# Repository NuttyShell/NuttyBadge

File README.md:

# NuttyBadge
NuttyBadge: A NuttyShell crafted security and hardware multi-tool. Open-sourced Hardware and Software.

## Hardware
[Click here for Hardware](NuttyHardware): Full Schematic and PCBs, along with BOM list

## Software
[Click here for Software](NuttyOS): Full Software based on ESP-IDF and FreeRTOS

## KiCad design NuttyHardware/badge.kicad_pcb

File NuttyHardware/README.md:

# NuttyBadge/NuttyHardware

---
# Hardware Changelog

## Latest hardware revision: Rev. C (May-2026)

Compared to Rev. B (June-2025), NuttyBadge Revision C has the following changes:

- Switched the main screen from LCD to OLED. SPI is still used, code changes are implemented to support both version of the NuttyBadge via a preprocessor marco.

- The physical screen size of the OLED screen is smaller, but the resolution is kept the same (128x64). Compared to the original LCD screen, OLED screen provides way better contrast level, no ghosting, and supports way higher framerate, which could potentially enable better experiences for fast moving objects like gaming scenes.

- As OLED is self-illuminating, there is no backlight. So now R11, R18 and Q2 are unpopulated. LCD_BL_PWM is unused and can be hacked for other purposes.

- Fixed a minor issue in Rev. B where the bypass capacitor (C49 and C51) for Y1 (USB Hub CH334R [U10]'s 12MHz USB Crystal) is wrong. With a 12pF shunt capacitance of the crystal, there is no need to populate C49 and C51. Just relying on the internal capacitors in the CH334R is sufficient.

---

Compared to Rev. A (Initial Version of June-2024), NuttyBadge Revision B has the following changes:

- LuatOS ESP32 Module has stopped production entirely. As the manufacturer refuses to sell the module with even no MOQ figures, we are forced to switch to use another module. We have completely abandoned the usage of 3rd party module and stick with original `ESP32-S3-WROOM-1-N16R8` module to avoid future supply chain problem.

- We included a USB HUB chip (CH334R) [U10] to allow the simultaneously usage of both usb-to-serial chip (CH343P) [U11] and ESP32S3 onboard USB device.

- Auto reset and program mode via DTR/RTS pins are fully implemented.

- Note: C49 and C51 values are incorrect, as CH334R contains an internal bypass cap for the crystal. The distributed boards had C49 and C51 removed. This will be fixed in NuttyBadge Rev. C.

- In terms of schematic hierarchy, we now have a dedicated schematic sheet for the ESP32S3 part of the circuit due to above reasons.

- Audio circuit is optmized and simplified. Now we just use a single N-FET (AO3400A) [Q4] to drive the buzzer [BZ1]. We expect this will further improve the sound quality and efficiency of the circuit.

- A Camera port is included in Rev. B. Although one already provided in the LuatOS module, the pins used might clash with PSRAM and are not carefully considered. Tested with OV2640 with fair results.

- Two LDOs are included to generate 1.2V and 2.8V rails to enable the usage of camera.

- LCD Backlight are driven with N-FET, this will make the driving circuit more efficient.

- For the main battery buck-boost converter, we have switched L1 from 2.2uH to 3.3uH, to provide better voltage ripple figures and reduce conduction losses in the expense of load transient response.

- We also wired the PS pin of TPS63001 to the positive rail, enabling power save mode to allow the overall circuit saving more power.

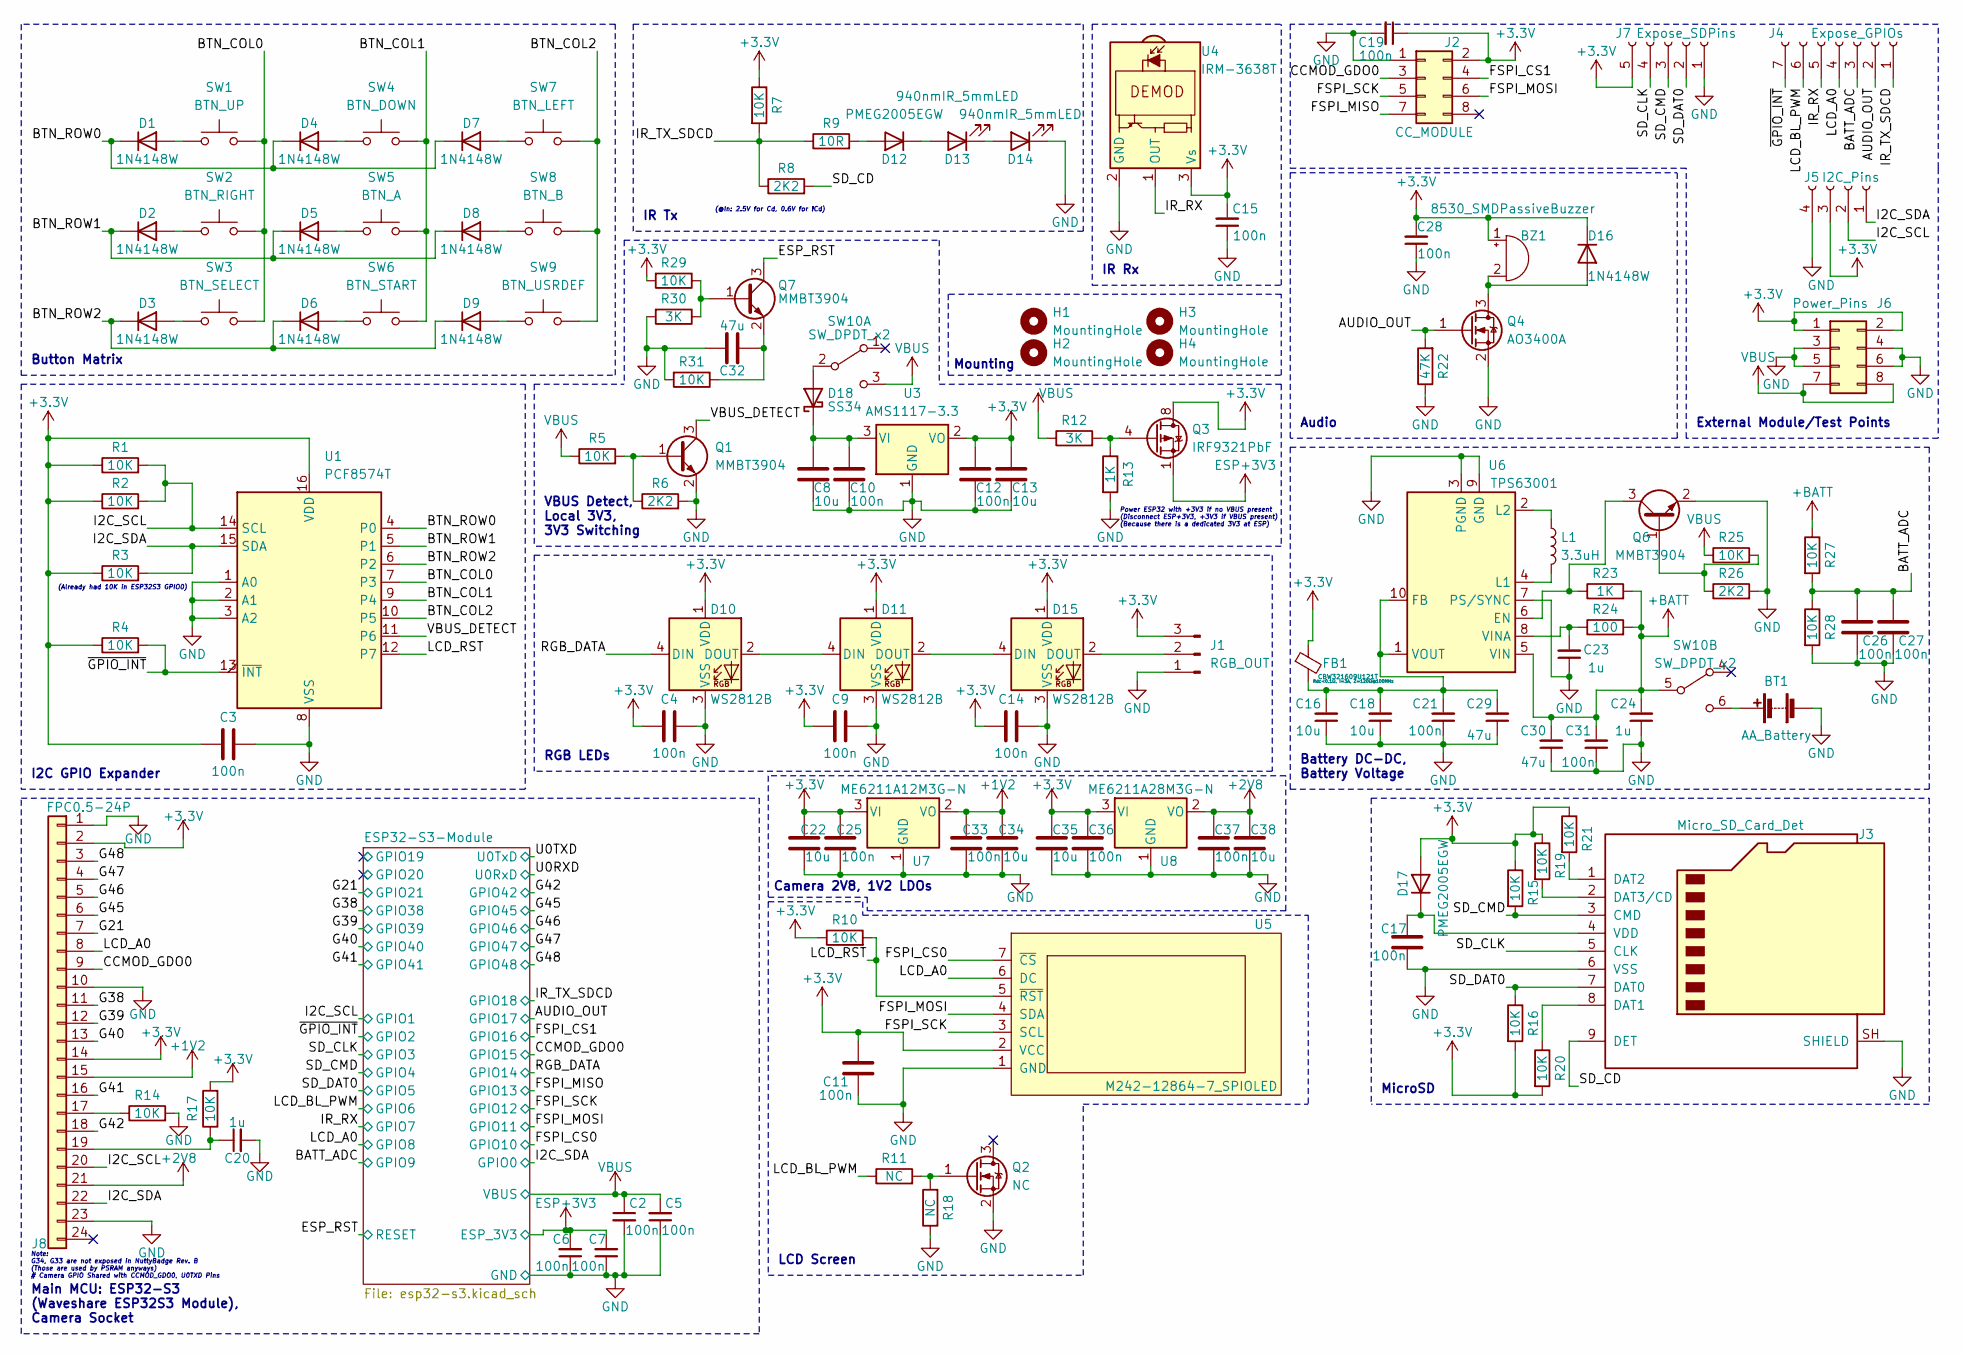
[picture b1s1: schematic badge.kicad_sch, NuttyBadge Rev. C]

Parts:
BT1: AA_Battery; BatteryHolder_2AA
BZ1: 8530_SMDPassiveBuzzer; MagneticBuzzer_Kobitone_254-EMB84Q-RO
C2, C3, C4, C5, C6, C7, C9, C10, C11, C12, C14, C15, C17, C19, C21, C25, C26, C27, C28, C31, C33, C36, C37: 100n; C_1206_3216Metric_Pad1.33x1.80mm_HandSolder
C8, C13, C16, C18, C22, C34, C35, C38: 10u; C_1206_3216Metric_Pad1.33x1.80mm_HandSolder
C20, C23, C24: 1u; C_1206_3216Metric_Pad1.33x1.80mm_HandSolder
C29, C30, C32: 47u; C_1206_3216Metric_Pad1.33x1.80mm_HandSolder
D1, D2, D3, D4, D5, D6, D7, D8, D9, D16: 1N4148W; D_SOD-123-BigDiodeSilkscreen
D10, D11, D15: WS2812B; LED_WS2812B_PLCC4_5.0x5.0mm_P3.2mm-TriangleSilkscreen
D12, D17: PMEG2005EGW; D_SOD-123-BigDiodeSilkscreen
D13, D14: 940nmIR_5mmLED; LED_D5.0mm_Horizontal_O3.81mm_Z3.0mm
D18: SS34; D_SMA_Handsoldering-BigDiodeSilkscreen
FB1: CBW321609U121T; L_1206_3216Metric_Pad1.42x1.75mm_HandSolder
H1, H2, H3, H4: MountingHole; MountingHole_3.2mm_M3_ISO7380
J1: RGB_OUT; PinHeader_1x03_P2.54mm_Vertical
J2: CC_MODULE; PinSocket_2x04_P2.54mm_Vertical_PinNumberFlipped
J3: Micro_SD_Card_Det; Conn_uSDcard
J4: Expose_GPIOs; PinHeader_1x07_P2.54mm_Vertical
J5: I2C_Pins; PinSocket_1x04_P2.54mm_Vertical
J6: Power_Pins; PinSocket_2x04_P2.54mm_Vertical_PinNumberFlipped
J7: Expose_SDPins; PinHeader_1x05_P2.54mm_Vertical
J8: FPC0.5-24P; Jushuo_AFC07-S24FCA-00_1x24-1MP_P0.50_Horizontal
L1: 3.3uH; L_Wuerth_HCI-1040
Q1, Q6, Q7: MMBT3904; SOT-23
Q2: NC; SOT-23
Q3: IRF9321PbF; SOIC-8_3.9x4.9mm_P1.27mm
Q4: AO3400A; SOT-23
R1, R2, R3, R4, R5, R7, R10, R14, R15, R16, R17, R19, R20, R21, R25, R27, R28, R29, R31: 10K; R_1206_3216Metric_Pad1.30x1.75mm_HandSolder
R6, R8, R26: 2K2; R_1206_3216Metric_Pad1.30x1.75mm_HandSolder
R9: 10R; R_1206_3216Metric_Pad1.30x1.75mm_HandSolder
R11, R18: NC; R_1206_3216Metric_Pad1.30x1.75mm_HandSolder
R12, R30: 3K; R_1206_3216Metric_Pad1.30x1.75mm_HandSolder
R13, R23: 1K; R_1206_3216Metric_Pad1.30x1.75mm_HandSolder
R22: 47K; R_1206_3216Metric_Pad1.30x1.75mm_HandSolder
R24: 100; R_1206_3216Metric_Pad1.30x1.75mm_HandSolder
SW1: BTN_UP; SW_Push_1P1T_NO_CK_PTS125Sx43PSMTR_NoHoles
SW2: BTN_RIGHT; SW_Push_1P1T_NO_CK_PTS125Sx43PSMTR_NoHoles
SW3: BTN_SELECT; SW_Push_1P1T_NO_CK_PTS125Sx43PSMTR_NoHoles
SW4: BTN_DOWN; SW_Push_1P1T_NO_CK_PTS125Sx43PSMTR_NoHoles
SW5: BTN_A; SW_Push_1P1T_NO_CK_PTS125Sx43PSMTR_NoHoles
SW6: BTN_START; SW_Push_1P1T_NO_CK_PTS125Sx43PSMTR_NoHoles
SW7: BTN_LEFT; SW_Push_1P1T_NO_CK_PTS125Sx43PSMTR_NoHoles
SW8: BTN_B; SW_Push_1P1T_NO_CK_PTS125Sx43PSMTR_NoHoles
SW9: BTN_USRDEF; SW_Push_1P1T_NO_CK_PTS125Sx43PSMTR_NoHoles
SW10: SW_DPDT_x2; SW_DPDT_Power_Switch
U1: PCF8574T; SOIC-16W_7.5x10.3mm_P1.27mm
U3: AMS1117-3.3; SOT-223-3_TabPin2
U4: IRM-3638T; Vishay_MINICAST-3Pin
U5: M242-12864-7_SPIOLED; M242-12864-7
U6: TPS63001; Texas_DRC0010J_ThermalVias_LargeHoles
U7: ME6211A12M3G-N; SOT-23-3
U8: ME6211A28M3G-N; SOT-23-3

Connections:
+1V2: C33.2, C34.2, J8.15, U7.2 (VO)
+2V8: C37.2, C38.2, J8.21, U8.2 (VO)
+3.3V: BZ1.1 (-), C3.1, C4.1, C9.1, C11.2, C12.2, C13.2, C14.1, C15.2, C19.1, C22.2, C25.2, C28.2, C35.2, C36.2, D10.1 (VDD), D11.1 (VDD), D15.1 (VDD), D16.1 (K), D17.2 (A), FB1.1, J1.3, J2.2, J5.3, J6.1, J6.2, J7.5, J8.2, J8.14, Q3.5 (D), Q3.6 (D), Q3.7 (D), Q3.8 (D), R1.1, R2.1, R3.1, R4.1, R7.1, R10.1, R15.1, R16.2, R17.2, R19.1, R20.2, R21.1, R29.2, U1.16 (VDD), U3.2 (VO), U4.3 (Vs), U5.2 (VCC), U7.3 (VI), U8.3 (VI)
+BATT: C24.2, C30.2, C31.2, R23.2, R24.2, R27.1, SW10.5 (B), U6.5 (VIN)
/AUDIO_OUT: J4.2, Q4.1 (G), R22.2; also elsewhere on the board
/BATT_ADC: C26.2, C27.2, J4.3, R27.2, R28.1; also elsewhere on the board
/BTN_COL0: SW1.2, SW2.2, SW3.2, U1.7 (P3)
/BTN_COL1: SW4.2, SW5.2, SW6.2, U1.9 (P4)
/BTN_COL2: SW7.2, SW8.2, SW9.2, U1.10 (P5)
/BTN_ROW0: D1.1 (K), D4.1 (K), D7.1 (K), U1.4 (P0)
/BTN_ROW1: D2.1 (K), D5.1 (K), D8.1 (K), U1.5 (P1)
/BTN_ROW2: D3.1 (K), D6.1 (K), D9.1 (K), U1.6 (P2)
/CCMOD_GDO0: J2.3, J8.9; also elsewhere on the board
/ESP_RST: Q7.3 (C); also elsewhere on the board
/FSPI_CS0: U5.7 (~CS); also elsewhere on the board
/FSPI_CS1: J2.4; also elsewhere on the board
/FSPI_MISO: J2.7; also elsewhere on the board
/FSPI_MOSI: J2.6, U5.4 (SDA); also elsewhere on the board
/FSPI_SCK: J2.5, U5.3 (SCL); also elsewhere on the board
/G21: J8.7; also elsewhere on the board
/G38: J8.11; also elsewhere on the board
/G39: J8.12; also elsewhere on the board
/G40: J8.13; also elsewhere on the board
/G41: J8.16; also elsewhere on the board
/G42: J8.18; also elsewhere on the board
/G45: J8.6; also elsewhere on the board
/G46: J8.5; also elsewhere on the board
/G47: J8.4; also elsewhere on the board
/G48: J8.3; also elsewhere on the board
/I2C_SCL: J5.2, J8.20, R1.2, R2.2, U1.14 (SCL); also elsewhere on the board
/I2C_SDA: J5.1, J8.22, R3.2, U1.15 (SDA); also elsewhere on the board
/IR_RX: J4.5, U4.1 (OUT); also elsewhere on the board
/IR_TX_SDCD: J4.1, R7.2, R8.1, R9.1; also elsewhere on the board
/LCD_A0: J4.4, J8.8, U5.6 (DC); also elsewhere on the board
/LCD_BL_PWM: J4.6, R11.1; also elsewhere on the board
/LCD_RST: R10.2, U1.12 (P7), U5.5 (~RST)
/RGB_DATA: D10.4 (DIN); also elsewhere on the board
/SD_CD: J3.9 (DET), R8.2
/SD_CLK: J3.5 (CLK), J7.4; also elsewhere on the board
/SD_CMD: J3.3 (CMD), J7.3, R15.2; also elsewhere on the board
/SD_DAT0: J3.7 (DAT0), J7.2, R16.1; also elsewhere on the board
/VBUS_DETECT: Q1.3 (C), U1.11 (P6)
/~GPIO_INT: J4.7, R4.2, U1.13 (~INT); also elsewhere on the board
ESP+3V3: C6.2, C7.2, Q3.1 (S), Q3.2 (S), Q3.3 (S); also elsewhere on the board
GND: BT1.2 (-), C2.2, C3.2, C4.2, C5.1, C6.1, C7.1, C8.1, C9.2, C10.1, C11.1, C12.1, C13.1, C14.2, C15.1, C16.1, C17.1, C18.1, C19.2, C20.2, C21.1, C22.1, C23.1, C24.1, C25.1, C26.1, C27.1, C28.1, C29.1, C30.1, C31.1, C32.1, C33.1, C34.1, C35.1, C36.1, C37.1, C38.1, D10.3 (VSS), D11.3 (VSS), D14.1 (K), D15.3 (VSS), J1.1, J2.1, J3.6 (VSS), J3.SH (SHIELD), J5.4, J6.3, J6.4, J6.5, J6.6, J7.1, J8.1, J8.10, J8.23, Q1.2 (E), Q2.2 (S), Q4.2 (S), Q6.2 (E), R6.2, R13.2, R14.2, R18.1, R22.1, R26.2, R28.2, R30.2, R31.2, U1.1 (A0), U1.2 (A1), U1.3 (A2), U1.8 (VSS), U3.1 (GND), U4.2 (GND), U5.1 (GND), U6.3 (PGND), U6.7 (PS/SYNC), U6.9 (GND), U6.11 (PGND), U7.1 (GND), U8.1 (GND); also elsewhere on the board
unnamed: BT1.1 (+), SW10.6 (C)
unnamed: BZ1.2 (+), D16.2 (A), Q4.3 (D)
unnamed: D1.2 (A), SW1.1
unnamed: D2.2 (A), SW2.1
unnamed: D3.2 (A), SW3.1
unnamed: D4.2 (A), SW4.1
unnamed: D5.2 (A), SW5.1
unnamed: D6.2 (A), SW6.1
unnamed: D7.2 (A), SW7.1
unnamed: D8.2 (A), SW8.1
unnamed: D9.2 (A), SW9.1
unnamed: D10.2 (DOUT), D11.4 (DIN)
unnamed: D11.2 (DOUT), D15.4 (DIN)
unnamed: D12.2 (A), R9.2
unnamed: D12.1 (K), D13.2 (A)
unnamed: D13.1 (K), D14.2 (A)
unnamed: D15.2 (DOUT), J1.2
unnamed: C17.2, D17.1 (K), J3.4 (VDD)
unnamed: D18.2 (A), SW10.2 (B)
unnamed: C8.2, C10.2, D18.1 (K), U3.3 (VI)
unnamed: J3.8 (DAT1), R20.1
unnamed: J3.1 (DAT2), R21.2
unnamed: J3.2 (DAT3/CD), R19.2
unnamed: J8.17, R14.1
unnamed: C20.1, J8.19, R17.1
unnamed: Q1.1 (B), R5.2, R6.1
unnamed: Q2.1 (G), R11.2, R18.2
unnamed: Q3.4 (G), R12.2, R13.1
unnamed: Q6.1 (B), R25.2, R26.1
unnamed: Q6.3 (C), R23.1, U6.6 (EN)
unnamed: Q7.1 (B), R29.1, R30.1
unnamed: C32.2, Q7.2 (E), R31.1
unnamed: C16.2, C18.2, C21.2, C29.2, FB1.2, U6.1 (VOUT), U6.10 (FB)
unnamed: L1.2, U6.4 (L1)
unnamed: L1.1, U6.2 (L2)
unnamed: C23.2, R24.1, U6.8 (VINA)
VBUS: C2.1, C5.2, J6.7, J6.8, R5.1, R12.1, R25.1, SW10.3 (C); also elsewhere on the board

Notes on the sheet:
Button Matrix
IR Rx
(@In: 2.5V for Cd, 0.6V for !Cd)
(Already had 10K in ESP32S3 GPIO0)
External Module/Test Points
Battery DC-DC, Battery Voltage
Main MCU: ESP32-S3 (Waveshare ESP32S3 Module), Camera Socket
Mounting
Audio
Note: G34, G33 are not exposed in NuttyBadge Rev. B (Those are used by PSRAM anyways) # Camera GPIO Shared with CCMOD_GDO0, U0TXD Pins
VBUS Detect, Local 3V3, 3V3 Switching
IR Tx
MicroSD
LCD Screen
Power ESP32 with +3V3 if no VBUS present (Disconnect ESP+3V3, +3V3 if VBUS present) (Because there is a dedicated 3V3 at ESP)
I2C GPIO Expander
Camera 2V8, 1V2 LDOs
RGB LEDs

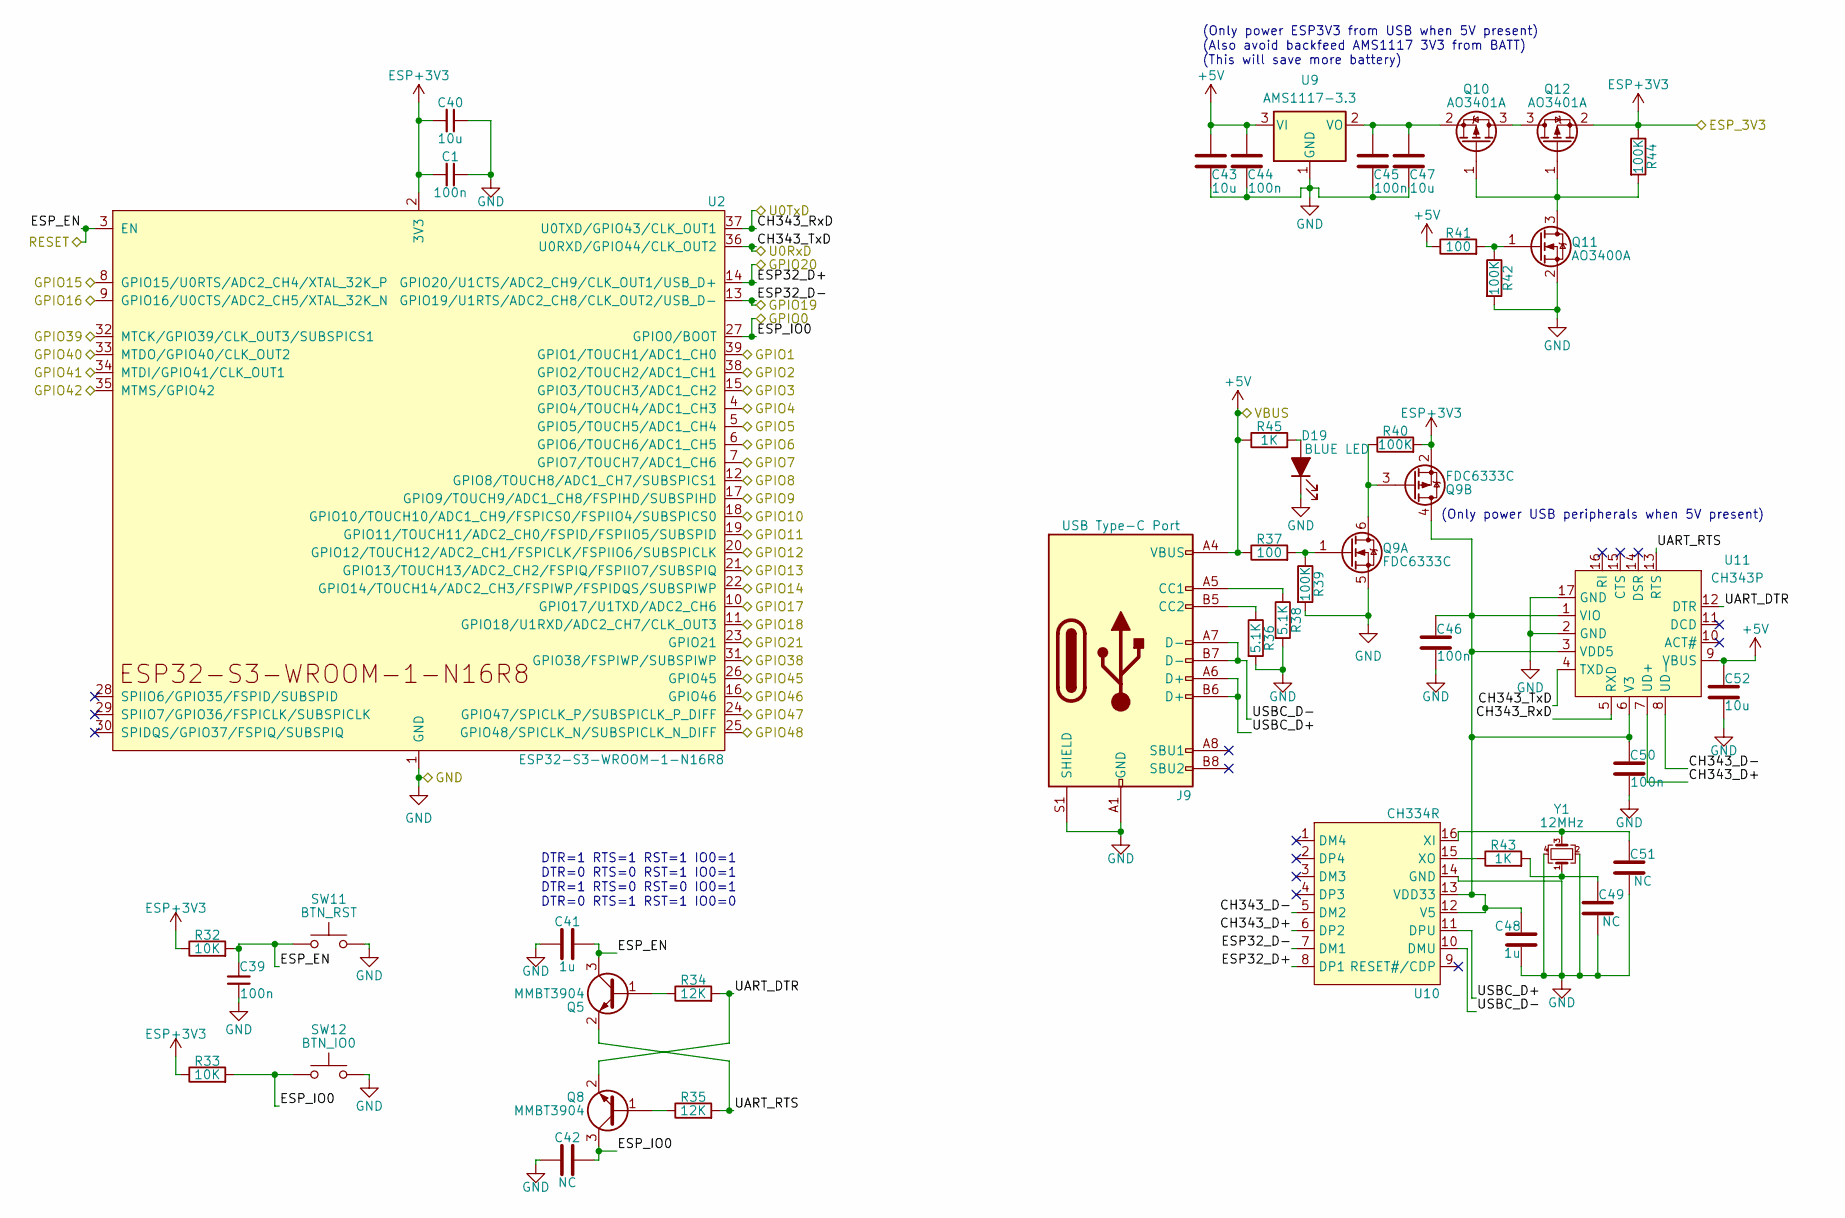
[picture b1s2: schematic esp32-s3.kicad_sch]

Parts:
C1, C39, C44, C45, C46, C50: 100n; C_1206_3216Metric_Pad1.33x1.80mm_HandSolder
C40, C43, C47, C52: 10u; C_1206_3216Metric_Pad1.33x1.80mm_HandSolder
C41, C48: 1u; C_1206_3216Metric_Pad1.33x1.80mm_HandSolder
C42, C49, C51: NC; C_1206_3216Metric_Pad1.33x1.80mm_HandSolder
D19: BLUE LED; LED_0805_2012Metric_Pad1.15x1.40mm_HandSolder-BigDiodeSilks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
J9: USB Type-C Port; USB_C_Receptacle_HRO_TYPE-C-31-M-12
Q5, Q8: MMBT3904; SOT-23
Q9: FDC6333C; TSOT-23-6
Q10, Q12: AO3401A; SOT-23
Q11: AO3400A; SOT-23
R32, R33: 10K; R_1206_3216Metric_Pad1.30x1.75mm_HandSolder
R34, R35: 12K; R_1206_3216Metric_Pad1.30x1.75mm_HandSolder
R36, R38: 5.1K; R_1206_3216Metric_Pad1.30x1.75mm_HandSolder
R37, R41: 100; R_1206_3216Metric_Pad1.30x1.75mm_HandSolder
R39, R40, R42, R44: 100K; R_1206_3216Metric_Pad1.30x1.75mm_HandSolder
R43, R45: 1K; R_1206_3216Metric_Pad1.30x1.75mm_HandSolder
SW11: BTN_RST; SW_Push_1P1T_NO_Vertical_Wuerth_434133025816
SW12: BTN_IO0; SW_Push_1P1T_NO_Vertical_Wuerth_434133025816
U2: ESP32-S3-WROOM-1-N16R8; ESP32-S3-WROOM-1
U9: AMS1117-3.3; SOT-223-3_TabPin2
U10: CH334R; QSOP-16_3.9x4.9mm_P0.635mm
U11: CH343P; QFN-16-1EP_3x3mm_P0.5mm_EP1.7x1.7mm
Y1: 12MHz; Crystal_SMD_3225-4Pin_3.2x2.5mm_HandSoldering

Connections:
/AUDIO_OUT: U2.10 (GPIO17/U1TXD/ADC2_CH6); also elsewhere on the board
/BATT_ADC: U2.17 (GPIO9/TOUCH9/ADC1_CH8/FSPIHD/SUBSPIHD); also elsewhere on the board
/CCMOD_GDO0: U2.8 (GPIO15/U0RTS/ADC2_CH4/XTAL_32K_P); also elsewhere on the board
/ESP32-S3-Module/CH343_D+: U10.6 (DP2), U11.7 (UD+)
/ESP32-S3-Module/CH343_D-: U10.5 (DM2), U11.8 (UD-)
/ESP32-S3-Module/ESP32_D+: U2.14 (GPIO20/U1CTS/ADC2_CH9/CLK_OUT1/USB_D+), U10.8 (DP1)
/ESP32-S3-Module/ESP32_D-: U2.13 (GPIO19/U1RTS/ADC2_CH8/CLK_OUT2/USB_D-), U10.7 (DM1)
/ESP32-S3-Module/UART_DTR: Q8.2 (E), R34.2, U11.12 (DTR)
/ESP32-S3-Module/UART_RTS: Q5.2 (E), R35.2, U11.13 (RTS)
/ESP32-S3-Module/USBC_D+: J9.A6 (D+), J9.B6 (D+), U10.11 (DPU)
/ESP32-S3-Module/USBC_D-: J9.A7 (D-), J9.B7 (D-), U10.10 (DMU)
/ESP_RST: C39.2, C41.2, Q5.3 (C), R32.2, SW11.1, U2.3 (EN); also elsewhere on the board
/FSPI_CS0: U2.18 (GPIO10/TOUCH10/ADC1_CH9/FSPICS0/FSPIIO4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); also elsewhere on the board
/FSPI_CS1: U2.9 (GPIO16/U0CTS/ADC2_CH5/XTAL_32K_N); also elsewhere on the board
/FSPI_MISO: U2.21 (GPIO13/TOUCH13/ADC2_CH2/FSPIQ/FSPIIO7/S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); also elsewhere on the board
/FSPI_MOSI: U2.19 (GPIO11/TOUCH11/ADC2_CH0/FSPID/FSPIIO5/S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); also elsewhere on the board
/FSPI_SCK: U2.20 (GPIO12/TOUCH12/ADC2_CH1/FSPICLK/FSPIIO6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); also elsewhere on the board
/G21: U2.23 (GPIO21); also elsewhere on the board
/G38: U2.31 (GPIO38/FSPIWP/SUBSPIWP); also elsewhere on the board
/G39: U2.32 (MTCK/GPIO39/CLK_OUT3/SUBSPICS1); also elsewhere on the board
/G40: U2.33 (MTDO/GPIO40/CLK_OUT2); also elsewhere on the board
/G41: U2.34 (MTDI/GPIO41/CLK_OUT1); also elsewhere on the board
/G42: U2.35 (MTMS/GPIO42); also elsewhere on the board
/G45: U2.26 (GPIO45); also elsewhere on the board
/G46: U2.16 (GPIO46); also elsewhere on the board
/G47: U2.24 (GPIO47/SPICLK_P/SUBSPICLK_P_DIFF); also elsewhere on the board
/G48: U2.25 (GPIO48/SPICLK_N/SUBSPICLK_N_DIFF); also elsewhere on the board
/I2C_SCL: U2.39 (GPIO1/TOUCH1/ADC1_CH0); also elsewhere on the board
/I2C_SDA: C42.2, Q8.3 (C), R33.2, SW12.1, U2.27 (GPIO0/BOOT); also elsewhere on the board
/IR_RX: U2.7 (GPIO7/TOUCH7/ADC1_CH6); also elsewhere on the board
/IR_TX_SDCD: U2.11 (GPIO18/U1RXD/ADC2_CH7/CLK_OUT3); also elsewhere on the board
/LCD_A0: U2.12 (GPIO8/TOUCH8/ADC1_CH7/SUBSPICS1); also elsewhere on the board
/LCD_BL_PWM: U2.6 (GPIO6/TOUCH6/ADC1_CH5); also elsewhere on the board
/RGB_DATA: U2.22 (GPIO14/TOUCH14/ADC2_CH3/FSPIWP/FSPIDQS/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); also elsewhere on the board
/SD_CLK: U2.15 (GPIO3/TOUCH3/ADC1_CH2); also elsewhere on the board
/SD_CMD: U2.4 (GPIO4/TOUCH4/ADC1_CH3); also elsewhere on the board
/SD_DAT0: U2.5 (GPIO5/TOUCH5/ADC1_CH4); also elsewhere on the board
/U0RXD: U2.36 (U0RXD/GPIO44/CLK_OUT2), U11.4 (TXD)
/U0TXD: U2.37 (U0TXD/GPIO43/CLK_OUT1), U11.5 (RXD)
/~GPIO_INT: U2.38 (GPIO2/TOUCH2/ADC1_CH1); also elsewhere on the board
ESP+3V3: C1.2, C40.2, Q9.2 (S), Q12.2 (S), R32.1, R33.1, R40.2, R44.1, U2.2 (3V3); also elsewhere on the board
GND: C1.1, C39.1, C40.1, C41.1, C42.1, C43.1, C44.1, C45.1, C46.1, C47.1, C48.1, C49.1, C50.1, C51.1, C52.1, D19.1 (K), J9.A1 (GND), J9.A12 (GND), J9.B1 (GND), J9.B12 (GND), J9.S1 (SHIELD), Q9.5 (S), Q11.2 (S), R36.2, R38.2, R39.2, R42.2, SW11.2, SW12.2, U2.1 (GND), U2.40 (GND), U2.41 (GND), U9.1 (GND), U10.14 (GND), U11.2 (GND), U11.17 (GND), Y1.2, Y1.4; also elsewhere on the board
unnamed: C49.2, R43.2, Y1.1
unnamed: D19.2 (A), R45.2
unnamed: J9.A5 (CC1), R38.1
unnamed: J9.B5 (CC2), R36.1
unnamed: Q5.1 (B), R34.1
unnamed: Q8.1 (B), R35.1
unnamed: Q9.3 (G), Q9.6 (D), R40.1
unnamed: Q9.1 (G), R37.2, R39.1
unnamed: C46.2, C48.2, C50.2, Q9.4 (D), U10.12 (V5), U10.13 (VDD33), U11.1 (VIO), U11.3 (VDD5), U11.6 (V3)
unnamed: Q10.3 (D), Q12.3 (D)
unnamed: Q10.1 (G), Q11.3 (D), Q12.1 (G), R44.2
unnamed: C45.2, C47.2, Q10.2 (S), U9.2 (VO)
unnamed: Q11.1 (G), R41.2, R42.1
unnamed: C51.2, U10.16 (XI), Y1.3
unnamed: R43.1, U10.15 (XO)
VBUS: C43.2, C44.2, C52.2, J9.A4 (VBUS), J9.A9 (VBUS), J9.B4 (VBUS), J9.B9 (VBUS), R37.1, R41.1, R45.1, U9.3 (VI), U11.9 (VBUS); also elsewhere on the board

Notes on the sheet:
(Only power ESP3V3 from USB when 5V present) (Also avoid backfeed AMS1117 3V3 from BATT) (This will save more battery)
DTR=1 RTS=1 RST=1 IO0=1 DTR=0 RTS=0 RST=1 IO0=1 DTR=1 RTS=0 RST=0 IO0=1 DTR=0 RTS=1 RST=1 IO0=0
(Only power USB peripherals when 5V present)

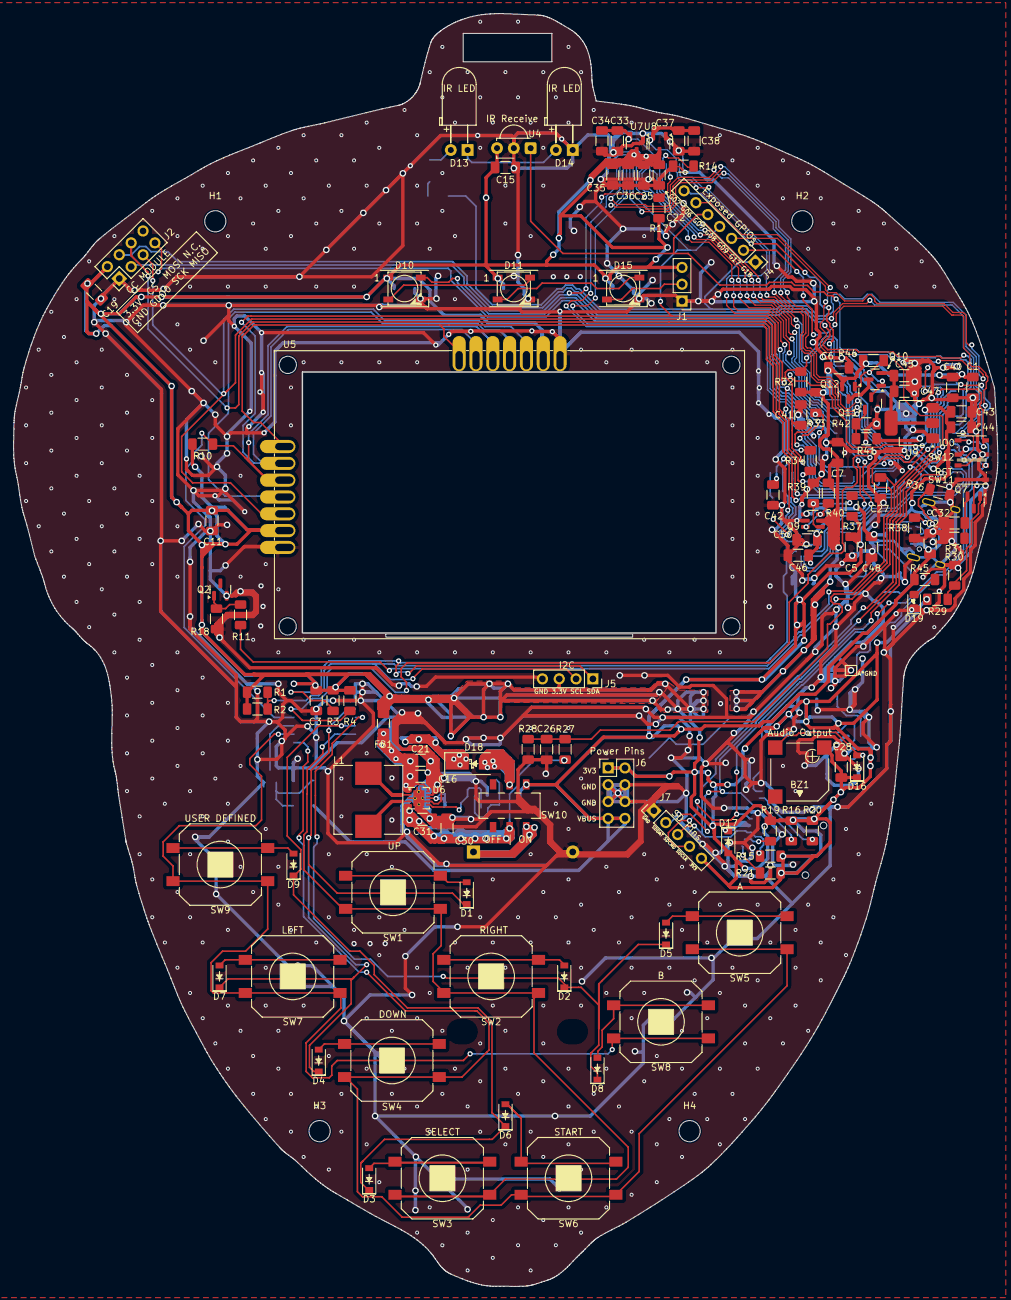
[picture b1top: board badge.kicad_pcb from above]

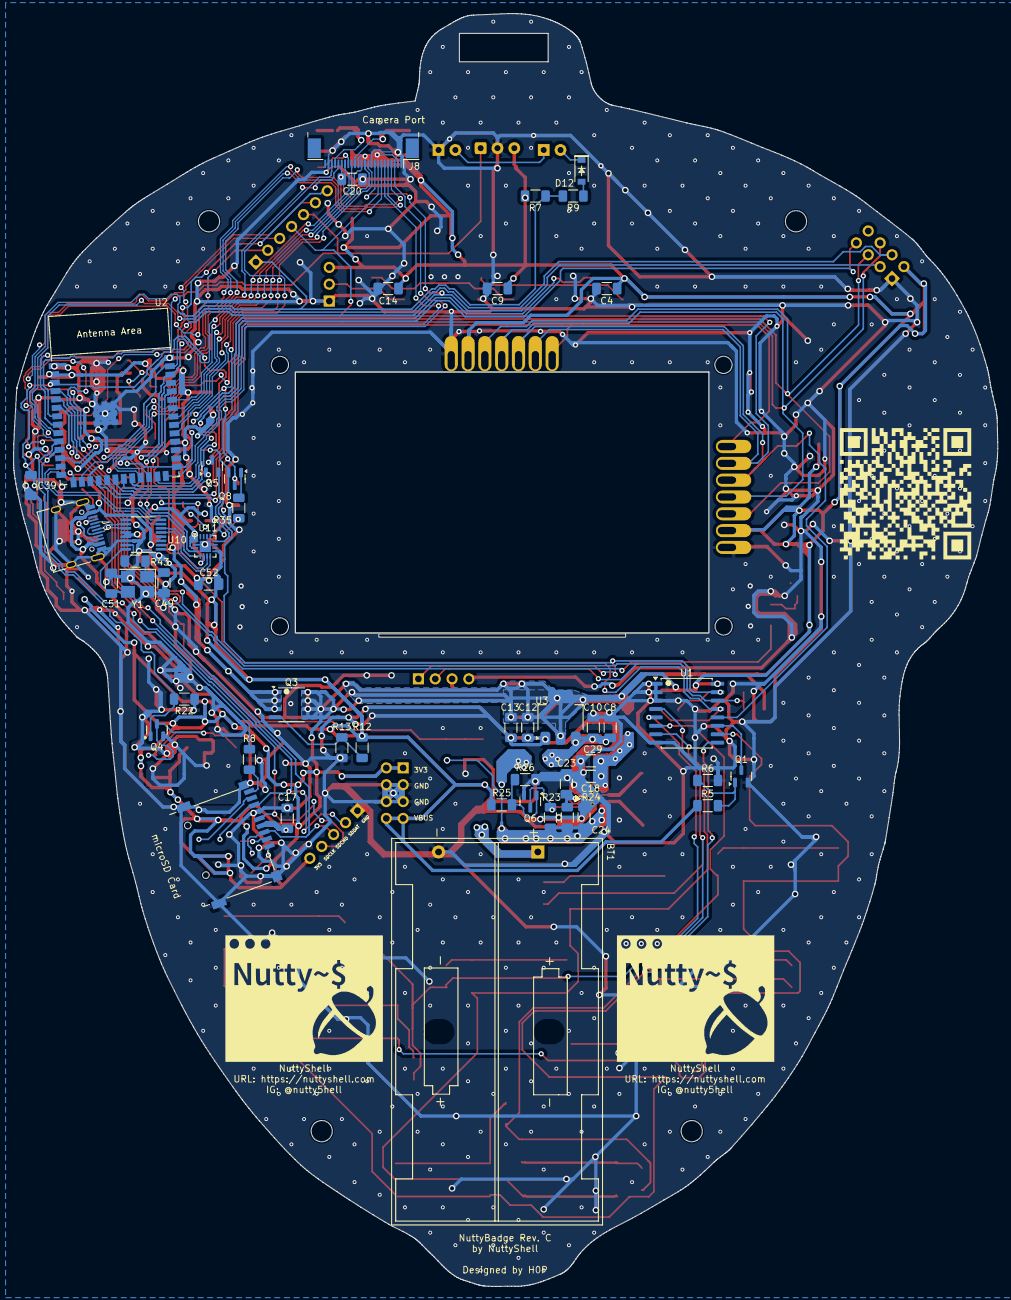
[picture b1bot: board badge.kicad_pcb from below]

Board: 2 copper layers, 148.6 x 192.2 mm, 169 parts (48 on the bottom side), 107 nets.

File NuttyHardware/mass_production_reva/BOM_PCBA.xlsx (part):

Reference(s) | 值 | LibPart | Footprint | 描述 | 封装 | 淘宝参考链接 | 类型
BT1 | AA_Battery | Device:Battery | Custom:BatteryHolder_2AA | 2节5号电池盒 | 直插电池盒 | https://item.taobao.com/item.htm?id=607322824447 | 直插
BZ1 | 8530_SMDPassiveBuzzer | Device:Buzzer | Buzzer_Beeper:MagneticBuzzer_Kobitone_254-EMB84Q-RO | MLT-8530 [3V] 电磁式贴片蜂鸣器 | 8530 | https://item.taobao.com/item.htm?id=555924156309 | 贴片
C1 | 100n | Device:C_Small | Capacitor_SMD:C_1206_3216Metric_Pad1.33x1.80mm_HandSolder | 104 ±10% 贴片电容 | 1206 | https://item.taobao.com/item.htm?id=635534146001 | 贴片
C2 | 100n | Device:C_Small | Capacitor_SMD:C_1206_3216Metric_Pad1.33x1.80mm_HandSolder | 104 ±10% 贴片电容 | 1206 | https://item.taobao.com/item.htm?id=635534146001 | 贴片
C3 | 100n | Device:C | Capacitor_SMD:C_1206_3216Metric_Pad1.33x1.80mm_HandSolder | 104 ±10% 贴片电容 | 1206 | https://item.taobao.com/item.htm?id=635534146001 | 贴片
C4 | 100n | Device:C | Capacitor_SMD:C_1206_3216Metric_Pad1.33x1.80mm_HandSolder | 104 ±10% 贴片电容 | 1206 | https://item.taobao.com/item.htm?id=635534146001 | 贴片
C5 | 100n | Device:C_Small | Capacitor_SMD:C_1206_3216Metric_Pad1.33x1.80mm_HandSolder | 104 ±10% 贴片电容 | 1206 | https://item.taobao.com/item.htm?id=635534146001 | 贴片
C6 | 100n | Device:C_Small | Capacitor_SMD:C_1206_3216Metric_Pad1.33x1.80mm_HandSolder | 104 ±10% 贴片电容 | 1206 | https://item.taobao.com/item.htm?id=635534146001 | 贴片
C7 | 100n | Device:C_Small | Capacitor_SMD:C_1206_3216Metric_Pad1.33x1.80mm_HandSolder | 104 ±10% 贴片电容 | 1206 | https://item.taobao.com/item.htm?id=635534146001 | 贴片
C8 | 10u | Device:C | Capacitor_SMD:C_1206_3216Metric_Pad1.33x1.80mm_HandSolder | 106 ±10% X5R 贴片电容 | 1206 | https://item.taobao.com/item.htm?id=537772527714 | 贴片
C9 | 100n | Device:C | Capacitor_SMD:C_1206_3216Metric_Pad1.33x1.80mm_HandSolder | 104 ±10% 贴片电容 | 1206 | https://item.taobao.com/item.htm?id=635534146001 | 贴片
C10 | 100n | Device:C | Capacitor_SMD:C_1206_3216Metric_Pad1.33x1.80mm_HandSolder | 104 ±10% 贴片电容 | 1206 | https://item.taobao.com/item.htm?id=635534146001 | 贴片
C11 | 100n | Device:C | Capacitor_SMD:C_1206_3216Metric_Pad1.33x1.80mm_HandSolder | 104 ±10% 贴片电容 | 1206 | https://item.taobao.com/item.htm?id=635534146001 | 贴片
C12 | 100n | Device:C | Capacitor_SMD:C_1206_3216Metric_Pad1.33x1.80mm_HandSolder | 104 ±10% 贴片电容 | 1206 | https://item.taobao.com/item.htm?id=635534146001 | 贴片
C13 | 10u | Device:C | Capacitor_SMD:C_1206_3216Metric_Pad1.33x1.80mm_HandSolder | 106 ±10% X5R 贴片电容 | 1206 | https://item.taobao.com/item.htm?id=537772527714 | 贴片
C14 | 100n | Device:C | Capacitor_SMD:C_1206_3216Metric_Pad1.33x1.80mm_HandSolder | 104 ±10% 贴片电容 | 1206 | https://item.taobao.com/item.htm?id=635534146001 | 贴片
C15 | 100n | Device:C_Small | Capacitor_SMD:C_1206_3216Metric_Pad1.33x1.80mm_HandSolder | 104 ±10% 贴片电容 | 1206 | https://item.taobao.com/item.htm?id=635534146001 | 贴片
C16 | 10u | Device:C_Small | Capacitor_SMD:C_1206_3216Metric_Pad1.33x1.80mm_HandSolder | 106 ±10% X5R 贴片电容 | 1206 | https://item.taobao.com/item.htm?id=537772527714 | 贴片
C17 | 100n | Device:C | Capacitor_SMD:C_1206_3216Metric_Pad1.33x1.80mm_HandSolder | 104 ±10% 贴片电容 | 1206 | https://item.taobao.com/item.htm?id=635534146001 | 贴片
C18 | 10u | Device:C_Small | Capacitor_SMD:C_1206_3216Metric_Pad1.33x1.80mm_HandSolder | 106 ±10% X5R 贴片电容 | 1206 | https://item.taobao.com/item.htm?id=537772527714 | 贴片
C19 | 100n | Device:C_Small | Capacitor_SMD:C_1206_3216Metric_Pad1.33x1.80mm_HandSolder | 104 ±10% 贴片电容 | 1206 | https://item.taobao.com/item.htm?id=635534146001 | 贴片
C20 | 10n | Device:C_Small | Capacitor_SMD:C_1206_3216Metric_Pad1.33x1.80mm_HandSolder | 103 ±10% 贴片电容 | 1206 | https://item.taobao.com/item.htm?id=523721859332 | 贴片
C21 | 100n | Device:C_Small | Capacitor_SMD:C_1206_3216Metric_Pad1.33x1.80mm_HandSolder | 104 ±10% 贴片电容 | 1206 | https://item.taobao.com/item.htm?id=635534146001 | 贴片
C22 | 1u | Device:C_Small | Capacitor_SMD:C_1206_3216Metric_Pad1.33x1.80mm_HandSolder | 105 ±10% X7R 贴片电容 | 1206 | https://item.taobao.com/item.htm?id=537884101441 | 贴片
C23 | 10u | Device:C_Small | Capacitor_SMD:C_1206_3216Metric_Pad1.33x1.80mm_HandSolder | 106 ±10% X5R 贴片电容 | 1206 | https://item.taobao.com/item.htm?id=537772527714 | 贴片
C24 | 10u | Device:C_Small | Capacitor_SMD:C_1206_3216Metric_Pad1.33x1.80mm_HandSolder | 106 ±10% X5R 贴片电容 | 1206 | https://item.taobao.com/item.htm?id=537772527714 | 贴片
C25 | NC | Device:C_Small | Capacitor_SMD:C_1206_3216Metric_Pad1.33x1.80mm_HandSolder | 不用焊接 | 不用焊接 | 不用焊接 | 不用焊接
C26 | 100n | Device:C | Capacitor_SMD:C_1206_3216Metric_Pad1.33x1.80mm_HandSolder | 104 ±10% 贴片电容 | 1206 | https://item.taobao.com/item.htm?id=635534146001 | 贴片
C27 | 100n | Device:C | Capacitor_SMD:C_1206_3216Metric_Pad1.33x1.80mm_HandSolder | 104 ±10% 贴片电容 | 1206 | https://item.taobao.com/item.htm?id=635534146001 | 贴片
C28 | 100n | Device:C_Small | Capacitor_SMD:C_1206_3216Metric_Pad1.33x1.80mm_HandSolder | 104 ±10% 贴片电容 | 1206 | https://item.taobao.com/item.htm?id=635534146001 | 贴片
C29 | 47u | Device:C_Small | Capacitor_SMD:C_1206_3216Metric_Pad1.33x1.80mm_HandSolder | 476 ±20% 6.3V X5R 贴片电容 | 1206 | https://item.taobao.com/item.htm?id=537932484854 | 贴片
C30 | 47u | Device:C_Small | Capacitor_SMD:C_1206_3216Metric_Pad1.33x1.80mm_HandSolder | 476 ±20% 6.3V X5R 贴片电容 | 1206 | https://item.taobao.com/item.htm?id=537932484854 | 贴片
C31 | 100n | Device:C_Small | Capacitor_SMD:C_1206_3216Metric_Pad1.33x1.80mm_HandSolder | 104 ±10% 贴片电容 | 1206 | https://item.taobao.com/item.htm?id=635534146001 | 贴片
C32 | 10u | Device:C | Capacitor_SMD:C_1206_3216Metric_Pad1.33x1.80mm_HandSolder | 106 ±10% X5R 贴片电容 | 1206 | https://item.taobao.com/item.htm?id=537772527714 | 贴片
D1 | 1N4148W | Diode:1N4148W | Custom:D_SOD-123-BigDiodeSilkscreen | 贴片开关二极管 | SOD-123 | https://item.taobao.com/item.htm?id=660511928550 | 贴片
D2 | 1N4148W | Diode:1N4148W | Custom:D_SOD-123-BigDiodeSilkscreen | 贴片开关二极管 | SOD-123 | https://item.taobao.com/item.htm?id=660511928550 | 贴片
D3 | 1N4148W | Diode:1N4148W | Custom:D_SOD-123-BigDiodeSilkscreen | 贴片开关二极管 | SOD-123 | https://item.taobao.com/item.htm?id=660511928550 | 贴片
D4 | 1N4148W | Diode:1N4148W | Custom:D_SOD-123-BigDiodeSilkscreen | 贴片开关二极管 | SOD-123 | https://item.taobao.com/item.htm?id=660511928550 | 贴片
D5 | 1N4148W | Diode:1N4148W | Custom:D_SOD-123-BigDiodeSilkscreen | 贴片开关二极管 | SOD-123 | https://item.taobao.com/item.htm?id=660511928550 | 贴片
D6 | 1N4148W | Diode:1N4148W | Custom:D_SOD-123-BigDiodeSilkscreen | 贴片开关二极管 | SOD-123 | https://item.taobao.com/item.htm?id=660511928550 | 贴片
D7 | 1N4148W | Diode:1N4148W | Custom:D_SOD-123-BigDiodeSilkscreen | 贴片开关二极管 | SOD-123 | https://item.taobao.com/item.htm?id=660511928550 | 贴片
D8 | 1N4148W | Diode:1N4148W | Custom:D_SOD-123-BigDiodeSilkscreen | 贴片开关二极管 | SOD-123 | https://item.taobao.com/item.htm?id=660511928550 | 贴片
D9 | 1N4148W | Diode:1N4148W | Custom:D_SOD-123-BigDiodeSilkscreen | 贴片开关二极管 | SOD-123 | https://item.taobao.com/item.htm?id=660511928550 | 贴片
D10 | WS2812B | LED:WS2812B | Custom:LED_WS2812B_PLCC4_5.0x5.0mm_P3.2mm-TriangleSilkscreen | RGB发光二极管 | 5050 | https://item.taobao.com/item.htm?id=686018450822 | 贴片
D11 | WS2812B | LED:WS2812B | Custom:LED_WS2812B_PLCC4_5.0x5.0mm_P3.2mm-TriangleSilkscreen | RGB发光二极管 | 5050 | https://item.taobao.com/item.htm?id=686018450822 | 贴片
D12 | PMEG2005EGW | Diode:1N4148W | Custom:D_SOD-123-BigDiodeSilkscreen | 低VF MEGA肖特基势垒整流器 | SOD-123 | https://item.taobao.com/item.htm?id=694851896900 | 贴片
D13 | 940nmIR_5mmLED | Device:LED | LED_THT:LED_D5.0mm_Horizontal_O3.81mm_Z3.0mm | 940nm红外发射二极管 | 5mm 直插 | https://item.taobao.com/item.htm?id=522572650100 | 直插
D14 | 940nmIR_5mmLED | Device:LED | LED_THT:LED_D5.0mm_Horizontal_O3.81mm_Z3.0mm | 940nm红外发射二极管 | 5mm 直插 | https://item.taobao.com/item.htm?id=522572650100 | 直插
D15 | WS2812B | LED:WS2812B | Custom:LED_WS2812B_PLCC4_5.0x5.0mm_P3.2mm-TriangleSilkscreen | RGB发光二极管 | 5050 | https://item.taobao.com/item.htm?id=686018450822 | 贴片
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
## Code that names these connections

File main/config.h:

#ifndef _CONFIG_h
#define _CONFIG_h

#include "driver/ledc.h"
#include "driver/gpio.h"
#include "esp_adc/adc_oneshot.h"

/****
G0 Strapping Pin (BOOT Mode), [I2C DATA]
G1 [I2C SCL]
G2 [IO EXAPNDER INTERRUPT]
G3-5 [SDIO for SD Card]
(Remember to Pull CMD, DATA to 3V3)*
G6 [LCD BL PWM]
G7 [IR RX]
G8 [LCD A0]
G9 [ADC1_CH8 for Battery Voltage Reading]
G10, G11, G12, G13 [FSPI for LCD, CC1101]
G10, G11 Board LED
G14 [WS2812b DATA]
G15 [CC1101 Interrupt]
G16 [CC1101 SPI CS]
G17 [AUDIO OUT]
G18 [IR TX/SD Card Detect]
G19, G20 ESP USB D-/D+
G21 On-board Camera Port
G26-G37 SPI FLASH/PSRAM
(G33-G37 = SPIIO4-7, SPIDQS)
G33-G42 On-board Camera Port
G43, G44 UART0
G45, G46 Strapping Pin (VDD_SPI Voltage, BOOT Mode)
G45-G48 On-board Camera Port
*/

#define GPIO_I2C_SDA      0  // I2C Bus SDA
#define GPIO_I2C_SCL      1  // I2C Bus SCL
#define GPIO_IOE_INT      2  // IO Expander Intrrupt
#define GPIO_IOE_INT_EDGE GPIO_INTR_NEGEDGE
#define GPIO_IOE_INT_ISR  ESP_INTR_FLAG_EDGE
#define GPIO_SD_CLK       3  // SD Card SD Bus CLK
#define GPIO_SD_CMD       4  // SD Card SD Bus CMD
#define GPIO_SD_DAT0      5  // SD Card SD Bus DAT0
#define GPIO_LCD_BL_PWM   6  // LCD Backlight PWM Out
#define GPIO_IR_RX        7  // IR Receive
#define GPIO_LCD_A0       8  // A0 Pin for LCD
#define GPIO_BATT_ADC     9  // Battery Readout Pin (Should use Analog, see next line)
#define ADC_BATT_ADC      -1 // Battery ADC
#define GPIO_LCD_CS       10 // CS Pin for LCD
#define GPIO_FSPI_MOSI    11 // FSPI MOSI Pin
#define GPIO_FSPI_SCK     12 // FSPI SCK Pin
#define GPIO_FSPI_MISO    13 // FSPI MISO Pin
#define GPIO_RGB_DATA     14 // WS2812B RGB Data Pin
#define GPIO_CCMOD_GDO0   15 // GDO0 Pin for CC Module
#define GPIO_CCMOD_CS     16 // CS Pin for CC Module
#define GPIO_AUDIO_OUT    17 // Audio PWM Out
#define GPIO_IR_TX_SDCD   18 // On Circuit Multiplexed for 2 functions: IR LED Transmit and SD Card Detect


#define LEDC_LCD_BL_PWM_DUTYRES LEDC_TIMER_8_BIT
#define LEDC_LCD_BL_PWM_FREQ 200000
#define LEDC_LCD_BL_PWM_SPEED LEDC_LOW_SPEED_MODE
#define LEDC_LCD_BL_PWM_CHANNEL LEDC_CHANNEL_0
#define LEDC_LCD_BL_PWM_TIMER LEDC_TIMER_1
#define LEDC_LCD_BL_PWM_INVERT 0

#define ADC_ATTEN ADC_ATTEN_DB_6
#define ADC_CHANNEL ADC_CHANNEL_8
#define ADC_UNIT ADC_UNIT_1
#define ADC_BITWIDTH ADC_BITWIDTH_DEFAULT
#define ADC_MV_ADJUST +2 // Account for ADC Input impedance, Voltage Divider Error, and ADC Atten Error

#define FSPI_HOST SPI2_HOST
#define LCD_SPEED_HZ (20*1000*1000)
#define CC_SPEED_HZ (10*1000*1000)

#define RMT_RGB_MEM_BLK_SYMBOLS 64
#define RMT_RGB_RESOLUTION_HZ 10000000
#define RGB_SHIFT_BITS 4
#define RGB_BULBS 3

#define RMT_IRTX_MEM_BLK_SYMBOLS 64
#define RMT_IRTX_RESOLUTION_HZ 1000000
#define RMT_IRRX_NEC_DECODE_MARGIN 200
#define RMT_IRRX_MEM_BLK_SYMBOLS 64
#define RMT_IRRX_RESOLUTION_HZ 1000000

#define IOE_I2C_ADDRESS 0x20

#define BTN_DEBOUNCE_PRESSED_THRESHOLD 5
#define BTN_DEBOUNCE_NOTPRESSED_THRESHOLD 3
#define BTN_HOLD_THRESHOLD 190

#define NUTTYSYSTEMMONITOR_LOW_BATTERY_THRESHOLD_MV 1900
#define NUTTYDISPLAY_INVERT_COLOR 1
#define NUTTYDISPLAY_USER_APP_AREA_WIDTH 128
#define NUTTYDISPLAY_USER_APP_AREA_HEIGHT 59
#define NUTTYDISPLAY_SYSTEM_TRAY_AREA_WIDTH 128
#define NUTTYDISPLAY_SYSTEM_TRAY_AREA_HEIGHT 5

#define SDCARD_MOUNT_POINT "/sdcard"

#define NUTTYOS_VERSION "v0.1a"

#endif /* _CONFIG_h */
